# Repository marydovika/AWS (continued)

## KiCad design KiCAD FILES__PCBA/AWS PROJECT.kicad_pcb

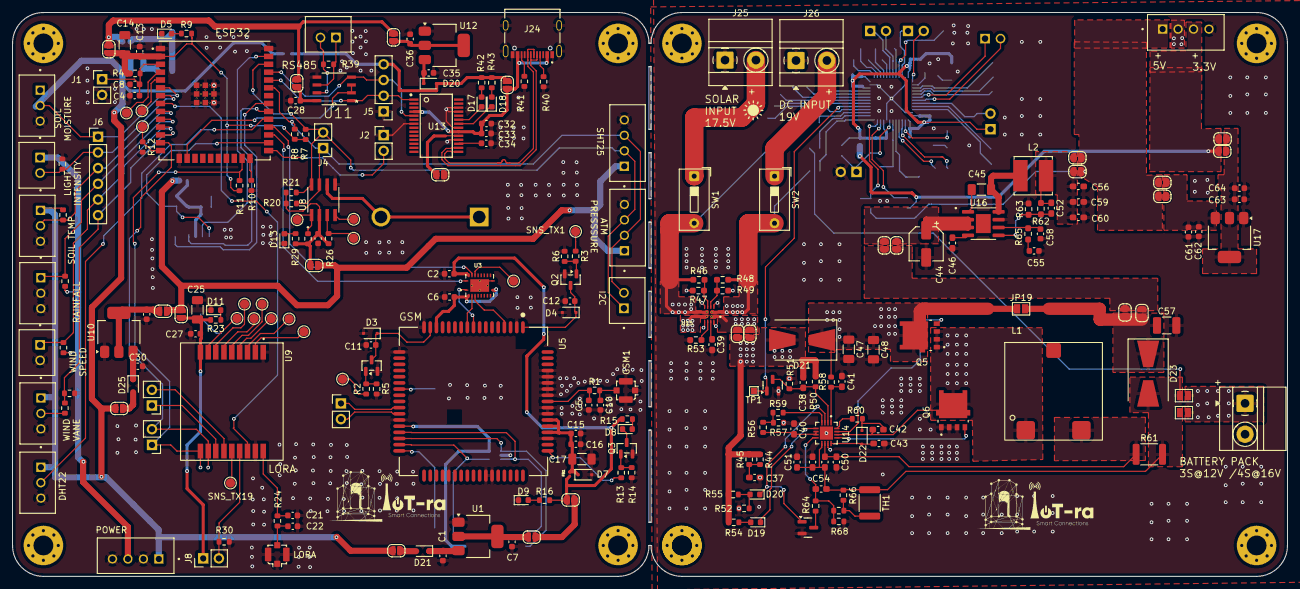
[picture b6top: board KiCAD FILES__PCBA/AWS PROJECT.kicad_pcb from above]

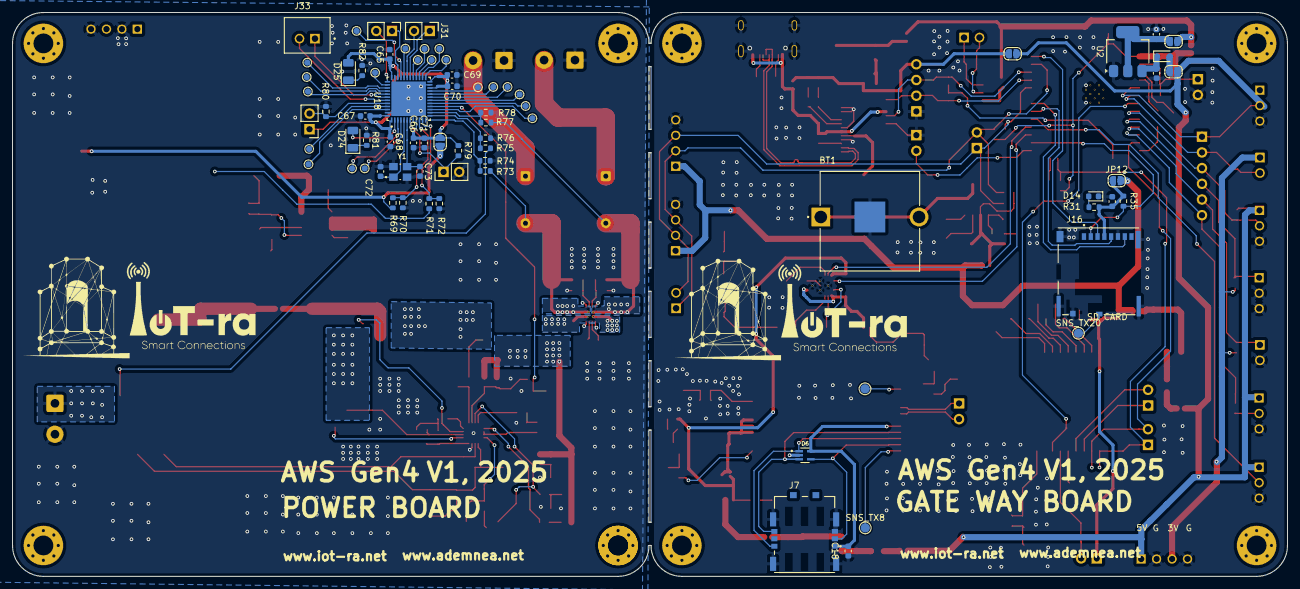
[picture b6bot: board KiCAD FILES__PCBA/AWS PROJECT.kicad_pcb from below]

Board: 2 copper layers, 206.3 x 91.2 mm, 308 parts (74 on the bottom side), 199 nets.

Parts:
BT1: BHX1-1225-PC; BAT_BHX1-1225-PC
C1, C3, C30, C35, C61, C62: 10uF; C_0603_1608Metric
C2, C4, C6, C11, C12, C13, C15, C18, C26, C27, C28, C33, C34, C65, C67, C69, C70: 0.1uF; C_0603_1608Metric
C5, C10, C21, C22: Cm; C_0603_1608Metric
C7, C8, C9, C16, C29, C31, C36, C63, C64: 1uF; C_0603_1608Metric
C14: 22uF; C_1206_3216Metric_Pad1.33x1.80mm_HandSolder
C17: 100uF; C_1206_3216Metric_Pad1.33x1.80mm_HandSolder
C25, C47, C48: 10uF; C_1206_3216Metric_Pad1.33x1.80mm_HandSolder
C32, C68, C71: 4.7uF; C_0603_1608Metric
C37, C49: 2.2uF; C_0603_1608Metric_Pad1.08x0.95mm_HandSolder
C38, C54: 22pF; C_0603_1608Metric_Pad1.08x0.95mm_HandSolder
C39: 0.01uF; C_0603_1608Metric_Pad1.08x0.95mm_HandSolder
C40, C41, C43, C53: 1uF; C_0603_1608Metric_Pad1.08x0.95mm_HandSolder
C42: 0.1uf; C_0603_1608Metric_Pad1.08x0.95mm_HandSolder
C44: 10uF; CP_Elec_5x5.8
C45: 100nF; C_1206_3216Metric_Pad1.33x1.80mm_HandSolder
C46: 10nF; C_0603_1608Metric_Pad1.08x0.95mm_HandSolder
C50: 0.1uF; C_0603_1608Metric_Pad1.08x0.95mm_HandSolder
C51: 10uF; C_0603_1608Metric_Pad1.08x0.95mm_HandSolder
C52: OPEN; C_0603_1608Metric_Pad1.08x0.95mm_HandSolder
C55: 2.7nF; C_0603_1608Metric
C56, C59, C60: 22uF; C_0603_1608Metric_Pad1.08x0.95mm_HandSolder
C57: 10uF; C_1210_3225Metric_Pad1.33x2.70mm_HandSolder
C58: 33pF; C_0603_1608Metric
C66: 10nF; C_0603_1608Metric
C72, C73: 22pF; C_0603_1608Metric
D3, D4, D7, D22: PESDHC3D3V3U; D_SOD-323F
D5, D8, D9, D11, D13, D14, D17, D18, D19, D20#2: NET_LED; D_0603_1608Metric
D6: ESDA6V1W5; SOT65P210X110-5N
D20, D21, D24, D25: 1N5819WS; D_SOD-323
D21#2, D23: B540C-13-F; D_SMB-SMC_Universal_Handsoldering
D24#2: green; LED_1206_3216Metric
D25#2: red; LED_1206_3216Metric
FB1: FerriteBead_Small; BEADC0603X33N
GSM1, GSM2: U.FL-R-SMT(10); U.FL_Molex_MCRF_73412-0110_Vertical
J1, J2, J3, J4, J8, J9, J10, J29, J30, J31, J32: Conn_01x02_Pin; PinHeader_1x02_P2.54mm_Vertical
J5: Conn_01x04_Pin; PinHeader_1x04_P2.54mm_Vertical
J6: Conn_01x06_Pin; PinHeader_1x06_P2.54mm_Vertical
J7: 104224-0820; MOLEX_104224-0820
J11, J15, J17, J28: B4B-XH-A_LF__SN_; JST_B4B-XH-A_LF__SN_
J12, J18, J19, J20, J22: B3B-XH-A_LF__SN_; JST_B3B-XH-A_LF__SN_
J13, J14, J21, J23, J33: B2B-XH-A_LF__SN_; JST_B2B-XH-A_LF__SN_
J16: 503398-1892; MOLEX_503398-1892
J24: TYPE-C-31-M-12; HRO_TYPE-C-31-M-12
J25, J26, J27: Screw_Terminal_01x02; TerminalBlock_MetzConnect_Type011_RT05502HBWC_1x02_P5.00mm_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
JP1, JP2, JP3, JP4, JP5, JP6, JP8, JP9, JP10, JP10#2, JP11, JP11#2, JP12, JP12#2, JP13, JP13#2, JP14, JP15, JP16, JP17, JP18, JP18#2, JP19#3, JP20, JP21, JP22, JP23, JP24, JP25: Jumper_2_Small_Open; SolderJumper-2_P1.3mm_Open_RoundedPad1.0x1.5mm
JP19, JP19#2, JP21#2: Jumper_2_Small_Open; SolderJumper-2_P1.3mm_Open_Pad1.0x1.5mm
L1: 6.1uH; CDEP147NP-6R1MC-95
L2: SRN6045TA-3R3Y; L_Bourns_SRN6045TA
PB1, PB2, PB3, PB4, PB5, PB6, PB7, PB8, PB9, PB10, PB11, PB12, PB13, PB14, PB15, PB16, PB17, PB18, PB19, PB20, PB21: TestPoint; TestPoint_Pad_D1.0mm
Q1, Q2, Q3: MMBT3904; SOT-23
Q4, Q7: 2N7002; Q_SOT-23
Q5, Q6: NMOS; TRANS_NVMFS5834NLWFT1G
R1, R24: 0R; R_0603_1608Metric
R2, R3, R5, R6, R7, R8, R13, R14, R20, R21, R25, R26, R32, R33, R38: 4.7k; R_0603_1608Metric
R4, R10, R11, R12, R30, R34: 10k; R_0603_1608Metric
R9, R15, R16, R23, R29, R31, R35: 1k; R_0603_1608Metric
R36: 20K; R_0603_1608Metric
R37, R54, R55, R69, R71, R73, R75, R77, R79, R80, R82: 10K; R_0603_1608Metric
R39: 120; R_0603_1608Metric
R40, R41: 5.1k; R_0603_1608Metric
R42, R43: 270R; R_0603_1608Metric
R44, R45: 3.9; R_0603_1608Metric
R46, R48: 23.7k; R_0603_1608Metric_Pad0.98x0.95mm_HandSolder
R47, R49: 5k; R_0603_1608Metric_Pad0.98x0.95mm_HandSolder
R50: 499K; R_0603_1608Metric
R51: 36K; R_0603_1608Metric
R52: 25k; R_0603_1608Metric
R53: 51.1K; R_0603_1608Metric_Pad0.98x0.95mm_HandSolder
R56: 5.23k; R_0603_1608Metric
R57: 7.5k; R_0603_1608Metric
R58: 10; R_0603_1608Metric
R59: 100; R_0603_1608Metric
R60: 2.2; R_0603_1608Metric
R61: 10; R_1812_4532Metric
R62, R63, R65: 5K1; R_0603_1608Metric_Pad0.98x0.95mm_HandSolder
R64: 4.22M; R_0603_1608Metric
R66: 154k; R_0603_1608Metric
R67: 887k; R_0603_1608Metric
R68: 162k; R_0603_1608Metric
R70: 20k; R_0603_1608Metric
R72: 13k; R_0603_1608Metric
R74: 1.5K; R_0603_1608Metric
R76: 2k; R_0603_1608Metric
R78: 1.2K; R_0603_1608Metric
R81: 330; R_0603_1608Metric
SNS_TX1, SNS_TX2, SNS_TX3, SNS_TX4, SNS_TX5, SNS_TX6, SNS_TX7, SNS_TX8, SNS_TX9, SNS_TX10, SNS_TX11, SNS_TX12, SNS_TX13, SNS_TX14, SNS_TX15, SNS_TX16, SNS_TX17, SNS_TX18, SNS_TX19, SNS_TX20: TestPoint; TestPoint_Pad_D1.5mm
SW1, SW2: SW_SPST; SW_DIP_SPSTx01_Slide_9.78x4.72mm_W7.62mm_P2.54mm
TH1: 100k; R_1812_4532Metric
TP1: TestPoint; TestPoint_Pad_1.0x1.0mm
U1, U2, U10, U12, U17: AMS1117-3.3; SOT-223-3_TabPin2
U3: TXB0108RGYR; IC_TXB0108RGYR
U4: ESP32-WROOM-32E__4MB_HIGH_TEMP_; MODULE_ESP32-WROOM-32UE_M113EH6400UH3Q0_
U5: SIM7000E; SIMCON_SIM7000E
U8: DS3231MZ_TRL; SOIC127P600X175-8N
U9: Ai-Thinker RA-08H; RA-08H
U11: ST3485EBDR; SOIC127P600X175-8N
U13: FT232RL-REEL; SOP65P780X200-28N
U14: BQ24650RVAR; QFN50P350X350X100-17N
U15: TPS2121RUXR; IC_TPS2121RUXR
U16: AP64501SP-13; SOIC127P600X170-9N
U18: STM32F401CCU6; QFN50P700X700X60-49N
Y1: C3E-25.000-12-3030-X-R; XTAL_C3E-25.000-12-3030-X-R

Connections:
3v3: J14.1, J15.3, R32.2, R33.2
5v: D20.2 (A), J5.4, J15.1, J18.1, J19.1, J20.1, J22.1, JP1.2 (B), JP2.2 (B), JP10#2.1 (A), JP10#2.2 (B), JP13.2 (B), JP15.2 (B), R38.2, R42.2, R43.2
+3.3V: J28.3, JP21.2 (B), JP24.2 (B), JP25.2 (B), R69.1
+3.3V_ESP: JP4.2 (B), JP5.2 (B), JP11#2.2 (B), JP16.2 (B)
+3.3V_GSM: JP3.2 (B), JP6.2 (B)
+3.3V_LORA: J11.1, J17.1, JP8.2 (B), JP10.2 (B), JP12#2.2 (B), JP14.2 (B)
+5V: J28.1, JP9.2 (B), JP12.2 (B), JP22.2 (B), JP23.2 (B), R71.1
/gate way/32khz: R25.1, SNS_TX11.1, U8.1 (32KHZ)
/gate way/-rs485 en: U4.16 (IO13), U11.2 (~RE), U11.3 (DE)
/gate way/D+: J3.1, U5.27 (USB_DP)
/gate way/D-: J3.2, U5.28 (USB_DM)
/gate way/DAVIS 7852: J6.4, J12.1, R32.1, U4.10 (IO25)
/gate way/DHT22: J22.2, U4.29 (IO5)
/gate way/DS18B20: J6.3, J20.2, R38.1, U4.9 (IO33)
/gate way/ESP32 power in: C13.1, C14.1, JP5.1 (A), R4.1, R7.2, R8.2, R9.2, R11.1, U4.2 (3V3)
/gate way/ESP_RX: U3.20 (B1), U4.27 (IO16)
/gate way/ESP_TX: U3.18 (B2), U4.28 (IO17)
/gate way/GSM_pw in: C2.1, FB1.2, JP6.1 (A), R15.2, R16.2, U3.19 (VCCB)
/gate way/I2C SCL: J4.2, J11.3, J17.2, J23.1, R7.1, R21.1, U4.36 (IO22), U8.8 (SCL)
/gate way/I2C SDA: J4.1, J11.2, J17.3, J23.2, R8.1, R20.1, U4.33 (IO21), U8.7 (SDA)
/gate way/INSPEED VORTEX: J6.5, J13.1, R33.1, U4.11 (IO26)
/gate way/INSPEEED VANE: J6.6, R36.2, R37.2, U4.12 (IO27)
/gate way/LORA ANT: C21.1, R24.1, U9.18 (ANT)
/gate way/LORA BOOT: J8.2, R30.2, U9.15 (IO2/BOOT)
/gate way/LORA RST: U4.8 (IO32), U9.16 (RST)
/gate way/LORA_RX: J10.2, U4.13 (IO14), U9.11 (TXD/IO17)
/gate way/LORA_TX: J10.1, R11.2, U4.23 (IO15), U9.10 (LPRXD/IO60)
/gate way/RI: SNS_TX5.1, U3.17 (B3)
/gate way/RS485 power in: C28.1, JP11#2.1 (A), U11.8 (VCC)
/gate way/RTC INT: R26.1, SNS_TX10.1, U8.3 (~INT/SQW)
/gate way/RTC RST: SNS_TX9.1, U8.4 (~RST)
/gate way/RTC power input: C26.1, JP10.1 (A), R20.2, R21.2, R25.2, R26.2, R29.2, U8.2 (VCC)
/gate way/S1223: J6.2, J14.2, R34.2, U4.7 (IO35)
/gate way/SD CS: J16.2 (CD/DAT3^2), R35.1, U4.26 (IO4)
/gate way/SD power in: C29.1, J16.4 (VDD), JP12#2.1 (A), R31.2, R35.2
/gate way/SIM CLK: D6.1, J7.S3 (CLK), U5.32 (SIM_CLK)
/gate way/SIM DATA: D6.3, J7.S6 (I/O), U5.31 (SIM_DATA)
/gate way/SIM DET: SNS_TX8.1, U5.34 (SIM_DET)
/gate way/SIM RST: D6.4, J7.S2 (RST), U5.33 (SIM_RST)
/gate way/SIM VDD: C18.1, D6.5, J7.S1 (VCC), U5.30 (SIM_VDD)
/gate way/USBD+: J24.A6 (DP1), J24.B6 (DP2), U13.15 (USBDP)
/gate way/USBD-: J24.A7 (DN1), J24.B7 (DN2), U13.16 (USBDM)
/gate way/VDD_EXT: C6.1, U3.2 (VCCA), U3.10 (OE), U5.15 (VDD_EXT)
/gate way/VH400: J6.1, J19.2, U4.6 (IO34)
/gate way/VSPI-CLK: J16.5 (CLK), U4.30 (IO18)
/gate way/VSPI-MISO: J16.7 (DAT0), U4.31 (IO19)
/gate way/VSPI-MOSI: J16.3 (CMD), U4.37 (IO23)
/gate way/gsm power key: R3.1, SNS_TX1.1
/gate way/gsm reset: R2.1, SNS_TX2.1
/gate way/gsm rx: U3.3 (A2), U5.10 (RXD)
/gate way/gsm tx: U3.1 (A1), U5.9 (TXD)
/gate way/lora power in: C25.1, C27.1, J8.1, JP8.1 (A), R23.2, U9.9 (VCC)
/gate way/main ant: C5.1, R1.1, U5.60 (RF_ANT)
/gate way/netlight: R13.1, U5.52 (NETLIGHT)
/gate way/nreset: C11.1, D3.1, Q1.3 (C), U5.16 (~NRESET)
/gate way/pwkey: C12.1, D4.1, Q2.3 (C), U5.1 (~PWRKEY)
/gate way/ri: U3.4 (A3), U5.4 (RI)
/gate way/rx: J5.2, U4.34 (RXD0), U11.1 (RO), U13.1 (TXD)
/gate way/strap2: R10.1, U4.24 (IO2)
/gate way/strap12: R12.1, SNS_TX7.1, U4.14 (IO12)
/gate way/tx: J5.3, U4.35 (TXD0), U11.4 (DI), U13.5 (RXD)
/power board/3V3_INPUT: R69.2, R70.1, U18.10 (PA0)
/power board/5V_INPUT: R71.2, R72.1, U18.11 (PA1)
/power board/BATTERY BMS: J27.1, JP19.2 (B), JP21#2.2 (B)
/power board/BATT_INPUT: R75.2, R76.1, U18.13 (PA3)
/power board/BATT_VAL: C49.2, C51.1, C53.1, C54.1, D23.2 (A), JP21#2.1 (A), R61.2, R66.2, R75.1, TH1.1, U14.9 (SRN)
/power board/BOOT0_MCU: J30.2, R80.2, U18.44 (BOOT0)
/power board/BOOT1_MCU: PB21.1, U18.20 (PB2)
/power board/CE: Q4.1 (G), TP1.1, U18.16 (PA6)
/power board/DC JACK INPUT: R48.1, R73.1, SW2.2 (B), U15.2 (IN2), U15.2_1 (IN2)
/power board/DC_INPUT: R73.2, R74.1, U18.12 (PA2)
/power board/FB: C52.2, R62.2, R63.1, U16.5 (FB)
/power board/MCU_SCL: J33.1, U18.42 (PB6)
/power board/MCU_SDA: J33.2, U18.43 (PB7)
/power board/MUXOUT: C38.1, D21#2.2 (A), JP13#2.2 (B), JP18.2 (B), R44.2, R45.2, R50.2, R54.2, R55.2
/power board/OV1: R46.2, R47.1, U15.5 (OV1)
/power board/OV2: R48.2, R49.1, U15.4 (OV2)
/power board/RST_MCU: J29.1, R79.1, U18.7 (~RST)
/power board/SOLAR INPUT: R46.1, R77.1, SW1.2 (B), U15.7 (IN1), U15.7_1 (IN1)
/power board/SOLAR_INPUT: R77.2, R78.1, U18.14 (PA4)
/power board/SW_AP: C45.1, L2.1, U16.8 (SW)
/power board/btst: R60.2, U14.16 (BTST)
/power board/cin: C72.2, U18.5 (PH0-OSC_IN), Y1.1
/power board/cout: C73.2, U18.6 (PH1-OSC_OUT), Y1.3
/power board/hidriv: Q5.4 (G), U14.15 (HIDRV)
/power board/lodriv: Q6.4 (G), U14.13 (LODRV)
/power board/mpptset: C38.2, Q4.3 (D), R50.1, R51.2, U14.2 (MPPSET)
/power board/ph: C42.2, L1.1, Q5.1 (S), Q5.2 (S), Q5.3 (S), Q6.5_6 (D), U14.14 (PH)
/power board/regn: C43.1, D22.2, U14.12 (REGN)
/power board/srp: C49.1, C50.1, L1.2, R61.1, U14.10 (SRP)
/power board/stat1: D19.1 (K), U14.5 (STAT2)
/power board/stat2: D20#2.1 (K), Q7.1 (G), U14.3 (STAT1)
/power board/ts: R59.2, U14.4 (TS)
/power board/vfb: C54.2, R64.2, R67.1, R68.2, U14.8 (VFB)
/power board/vref: C40.1, R56.2, U14.6 (VREF), U14.7 (TERM_EN)
GND: BT1.2, C1.2, C2.2, C3.2, C4.1, C5.2, C6.2, C7.2, C8.2, C9.2, C10.2, C11.2, C12.2, C13.2, C14.2, C15.2, C16.2, C17.2, C18.2, C21.2, C22.2, C25.2, C26.2, C27.2, C28.2, C29.2, C30.2, C31.2, C32.2, C33.2, C34.2, C35.2, C36.2, C37.2, C39.2, C40.2, C41.2, C43.2, C44.2, C46.2, C47.2, C48.2, C50.2, C51.2, C53.2, C55.2, C56.2, C57.2, C58.2, C59.2, C60.2, C61.2, C62.2, C63.2, C64.2, C65.2, C66.2, C67.2, C68.2, C69.2, C70.2, C71.2, C72.1, C73.1, D3.2, D4.2, D5.1 (K), D6.2, D7.2, D9.1 (K), D11.1 (K), D13.1 (K), D14.1 (K), GSM1.2, GSM2.2, J1.2, J2.1, J5.1, J7.G1 (GND), J7.G2 (GND), J7.G3 (GND), J7.G4 (GND), J7.S4 (GND), J11.4, J12.2, J12.3, J13.2, J15.2, J15.4, J16.6 (VSS), J16.9 (VSS), J16.P1 (SHIELD), J16.P2 (SHIELD), J16.P3 (SHIELD), J16.P4 (SHIELD), J17.4, J18.3, J19.3, J20.3, J22.3, J24.A1_B12 (GND), J24.B1_A12 (GND), J24.S1 (SHIELD), J24.S2 (SHIELD), J24.S3 (SHIELD), J24.S4 (SHIELD), J25.1, J26.1, J27.2, J28.2, J28.4, J29.2, JP17.2 (B), Q1.2 (E), Q2.2 (E), Q3.2 (E), Q4.2 (S), Q6.1 (S), Q6.2 (S), Q6.3 (S), Q7.2 (S), R5.1, R6.1, R10.2, R12.2, R14.1, R30.1, R34.1, R36.1, R40.1, R41.1, R47.2, R49.2, R51.1, R52.1, R53.2, R57.1, R63.2, R68.1, R70.2, R72.2, R74.2, R76.2, R78.2, R80.1, R81.1, R82.1, U1.1 (GND), U2.1 (GND), U3.11 (GND), U3.21 (EXP), U3.21_1 (EXP), U3.21_2 (EXP), U3.21_3 (EXP), U3.21_4 (EXP), U4.1 (GND), U4.15 (GND), U4.38 (GND), U4.39_1 (GND), U4.39_2 (GND), U4.39_3 (GND), U4.39_4 (GND), U4.39_5 (GND), U4.39_6 (GND), U4.39_7 (GND), U4.39_8 (GND), U4.39_9 (GND), U5.2 (GND), U5.17 (GND), U5.18 (GND), U5.29 (GND), U5.39 (GND), U5.45 (GND), U5.46 (GND), U5.54 (GND), U5.58 (GND), U5.59 (GND), U5.61 (GND), U5.62 (GND), U5.63 (GND), U5.64 (GND), U5.65 (GND), U8.5 (GND), U9.1 (GND), U9.17 (GND), U10.1 (GND), U11.5 (GND), U12.1 (GND), U13.7 (GND), U13.18 (GND), U13.21 (GND), U13.25 (AGND), U13.26 (TEST), U14.11 (GND), U14.17 (EP), U15.3 (CP2), U15.6 (PR1), U15.9 (ST), U15.12 (GND), U16.7 (GND), U17.1 (GND), U18.8 (VSSA/VREF-), U18.23 (VSS), U18.35 (VSS), U18.47 (VSS), U18.49 (EXP), Y1.2 (GND), Y1.4 (GND)
unnamed: C10.1, GSM1.1, R1.2
unnamed: C15.1, C16.1, C17.1, D7.1, FB1.1, U5.55 (VBAT), U5.56 (VBAT), U5.57 (VBAT)
unnamed: C22.1, GSM2.1, R24.2
unnamed: C37.1, R44.1, R45.1
unnamed: C42.1, D22.1, R60.1
unnamed: C55.1, R65.1
unnamed: D5.2 (A), R9.1
unnamed: D8.2 (A), R15.1
unnamed: D8.1 (K), Q3.3 (C)
unnamed: D9.2 (A), R16.1
unnamed: D11.2 (A), R23.1
unnamed: D13.2 (A), R29.1
unnamed: D14.2 (A), R31.1
unnamed: D17.2 (A), R42.1
unnamed: D17.1 (K), U13.23 (CBUS0)
unnamed: D18.2 (A), R43.1
unnamed: D18.1 (K), U13.22 (CBUS1)
unnamed: D19.2 (A), R54.1
unnamed: D20#2.2 (A), R52.2, R55.1
unnamed: C47.1, C48.1, C57.1, D21#2.1 (K), D23.1 (K), JP18#2.1 (A), JP19#2.1 (A), JP19#2.2 (B), JP20.1 (A), Q5.5_6 (D), R58.2
unnamed: D24#2.2 (A), U18.2 (PC13)
unnamed: D24#2.1 (K), R81.2
unnamed: D25.2 (A), JP13.1 (A)
unnamed: D25#2.1 (K), R82.2
unnamed: C4.2, C8.1, J1.1, R4.2, U4.3 (EN)
unnamed: J2.2, U4.25 (IO0)
unnamed: J9.1, U9.12 (RXD/IO16)
unnamed: J9.2, U9.13 (IO15)
unnamed: J16.10 (DETECT_SWITCH), SNS_TX20.1
unnamed: J18.2, R37.1
unnamed: J24.A5 (CC1), R40.2
unnamed: J24.B5 (CC2), R41.2
unnamed: J25.2, SW1.1 (A)
unnamed: J26.2, SW2.1 (A)
unnamed: J31.1, U18.30 (PA9)
unnamed: J31.2, U18.31 (PA10)
unnamed: J32.1, U18.34 (PA13/JTMS-SWDIO)
unnamed: J32.2, U18.37 (PA14/JTCK-SWCLK)
unnamed: D24.2 (A), JP2.1 (A)
unnamed: C7.1, JP3.1 (A), U1.2 (VO)
unnamed: C9.1, JP4.1 (A), U2.2 (VO)
unnamed: JP13#2.1 (A), JP18.1 (A), U15.1 (OUT), U15.1_1 (OUT), U15.8 (OUT), U15.8_1 (OUT)
unnamed: C31.1, JP14.1 (A), U10.2 (VO)
unnamed: C36.1, JP16.1 (A), U12.2 (VO)
unnamed: JP17.1 (A), U13.19 (~RESET)
unnamed: C44.1, JP19#3.1 (A), U16.2 (VIN), U16.3 (EN)
unnamed: C52.1, C56.1, C59.1, C60.1, JP22.1 (A), L2.2, R62.1
unnamed: C61.1, C62.1, JP23.1 (A), U17.3 (VI)
unnamed: C63.1, C64.1, JP24.1 (A), U17.2 (VO)
unnamed: Q1.1 (B), R2.2, R5.2
unnamed: Q2.1 (B), R3.2, R6.2
unnamed: Q3.1 (B), R13.2, R14.2
unnamed: Q7.3 (D), R64.1
unnamed: R56.1, R57.2, R59.1
unnamed: R66.1, R67.2, TH1.2
unnamed: C1.1, D21.1 (K), U1.3 (VI)
unnamed: C3.1, D24.1 (K), U2.3 (VI)
unnamed: SNS_TX4.1, U4.5 (SENSOR_VN)
unnamed: SNS_TX3.1, U4.4 (SENSOR_VP)
unnamed: SNS_TX6.1, U5.24 (USB_VBUS)
unnamed: BT1.1, BT1.1_1, U8.6 (VBAT)
unnamed: SNS_TX17.1, U9.5 (IO4)
unnamed: SNS_TX18.1, U9.6 (IO5)
unnamed: SNS_TX14.1, U9.2 (IO8)
unnamed: SNS_TX16.1, U9.4 (IO9)
unnamed: SNS_TX15.1, U9.3 (IO11)
unnamed: SNS_TX19.1, U9.14 (IO14)
unnamed: SNS_TX12.1, U9.7 (SWC/IO7)
unnamed: SNS_TX13.1, U9.8 (SWD/IO6)
unnamed: C30.1, D25.1 (K), U10.3 (VI)
unnamed: J21.1, R39.2, U11.6 (A)
unnamed: J21.2, R39.1, U11.7 (B)
unnamed: C35.1, U12.3 (VI)
unnamed: C34.1, U13.17 (3V3OUT)
unnamed: C41.1, R58.1, U14.1 (VCC)
unnamed: R53.1, U15.10 (ILIM)
unnamed: C39.1, U15.11 (SS)
unnamed: C45.2, U16.1 (BST)
unnamed: C58.1, R65.2, U16.6 (COMP)
unnamed: C46.1, U16.4 (SS)
unnamed: PB1.1, U18.15 (PA5)
unnamed: PB2.1, U18.17 (PA7)
unnamed: PB3.1, U18.29 (PA8)
unnamed: PB5.1, U18.32 (PA11)
unnamed: PB4.1, U18.33 (PA12)
unnamed: PB6.1, U18.38 (PA15/JTDI)
unnamed: PB7.1, U18.18 (PB0)
unnamed: PB8.1, U18.19 (PB1)
unnamed: PB9.1, U18.39 (PB3/JTDO-SWO)
unnamed: PB10.1, U18.40 (PB4/~JTRST)
unnamed: PB11.1, U18.41 (PB5)
unnamed: PB12.1, U18.45 (PB8)
unnamed: PB13.1, U18.46 (PB9)
unnamed: PB14.1, U18.21 (PB10)
unnamed: PB15.1, U18.25 (PB12)
unnamed: PB16.1, U18.26 (PB13)
unnamed: PB17.1, U18.27 (PB14)
unnamed: PB18.1, U18.28 (PB15)
unnamed: PB19.1, U18.3 (PC14-OSC32_IN)
unnamed: PB20.1, U18.4 (PC15-OSC32_OUT)
VBUS: C32.1, C33.1, J24.A4_B9 (VBUS), J24.B4_A9 (VBUS), JP15.1 (A), U13.4 (VCCIO), U13.20 (VCC)
VDD: C65.1, C66.1, C67.1, C68.1, C69.1, C70.1, C71.1, D25#2.2 (A), J30.1, JP25.1 (A), R79.2, U18.1 (VBAT), U18.9 (VDDA/VREF+), U18.22 (VCAP_1), U18.24 (VDD), U18.36 (VDD), U18.48 (VDD)
Vbuck: JP11.2 (B), JP18#2.2 (B), JP19#3.2 (B), JP20.2 (B)

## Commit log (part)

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2025-10-31 schematic version 1
2025-11-01 finalised schematic
2025-11-03 first pcb draft
2025-11-06 finalised power schematic
2025-11-14 commit 111
2025-12-19 algorirthim design start
2025-12-19 algorithim dev
2025-12-19 Add lock file for schematic with hostname and username information
2025-12-19 Refactor code structure for improved readability and maintainability
2025-12-20 updates to the code and hardware, testing complete
2025-12-21 updates to gateway board
2025-12-26 updates to the power board
2025-12-31 changes tp gateway bosrd
2025-12-31 updates to pcb color
2025-12-31 comment
2025-12-31 refactoring folder
2025-12-31 ccommit 1
2025-12-31 changes to schematic
2026-01-01 further changes
2026-01-01 All files
    Adding all files from local drive
2026-01-01 re-organizing files
    organizing folders for readability
2026-01-01 re-naming folders from local drive
2026-01-01 assigning 3D foot prints
2026-01-01 adding system images for current design and previous design
2026-01-01 updating 3D footprints on PCB
2026-01-02 BOM used for prototyping
2026-01-02 Added project reports
2026-01-03 Prototype Report
2026-01-03 Update AWS Prototyping Report document
    Revised the AWS_Prototyping_Report.docx file with new content or corrections.
2026-01-04 modified Prototyping report
2026-01-05 Add Davis rain gauge functionality and update main setup
2026-01-06 Implement wind speed and direction sensor classes; update DAVIS class for improved rain gauge functionality
2026-01-07 fixed i2c error on pcb, added power monitoring code, tested all i2c slaves
2026-01-07 updates to the gateway board
2026-01-07 cosmetic updates to pcb boards
2026-01-07 RESTRUCTURING FILES
2026-01-08 MODIFACTIONS TO CASE DESIGN
2026-01-08 adding vents to case
2026-01-12 updates to main
2026-01-19 footprints, text, logo alignment and report
2026-01-26 updates to gsm code, connected to things speak,
2026-01-26 reset active layer to default in project configuration
2026-01-28 changes to pcb and 3d mdel
2026-01-29 updates to board
2026-02-02 deleting documents from public
2026-02-04 resolving merge
2026-02-04 Add research overview for AWS power electronics
    Added a detailed overview of the research on modular and adaptive power electronics for Automatic Weather Stations (AWS).
2026-02-04 Refactor README for clarity and formatting
2026-02-04 Fix spelling error in README.md
    Corrected spelling of 'energy' in the README.
2026-02-04 Fix typo in README.md
    Corrected the spelling of 'tailered' to 'tailored' in the README.
2026-02-04 Revise README for clarity on modular power system
    Updated the description of the modular power electronics system to clarify energy source integration and control strategy.
2026-02-04 Update README with project funding and deployment details
    Added funding information and details about field deployment.
2026-02-16 edits to the boards, got lcsc part numbers for bom, swapped unavailable components, fixed net label confilcts
2026-02-16 further updates to board
2026-02-21 updates to pcb board and creation of BOM
2026-04-28 Revise README for clarity on project objectives
    Refined system description for the modular and adaptive power electronics architecture for AWS. Enhanced clarity and structure in outlining the project's goals, methodologies, and expected outcomes.
2026-06-16 ErrorLogger: add header guard, includes and log filename
2026-06-16 ErrorLogger: add component identifier defines
2026-06-16 ErrorLogger: add error type defines for RTC, BME280, DHT22, DS18B20, power monitor
2026-06-16 ErrorLogger: add error type defines for GSM, LoRa, SD, SIM, WiFi, sensors, main loop
2026-06-16 ErrorLogger: add class declaration - header file complete
2026-06-16 fix gsm error
2026-06-16 ErrorLogger: add static members and begin() function
2026-06-16 ErrorLogger: add log() function
2026-06-16 ErrorLogger: add errorCount() and printLast() functions
2026-06-16 ErrorLogger: add timestamp, SD write and serial write functions - implementation complete
2026-06-16 ErrorLogger: integrate into RTC.cpp - log not found, power loss, NTP sync fail
2026-06-16 Data estimation in gsm
2026-06-16 adding wifi broadcasting to configure sleep mode
2026-06-16 changed wifi-name
2026-06-17 ErrorLogger: integrate into AIR_PRESSURE.cpp - log sensor not found
2026-06-17 ErrorLogger: integrate into DHT22.cpp - log temp and humidity NaN failures
2026-06-17 ErrorLogger: integrate into SOILTEMP.cpp - log sensor disconnection
2026-06-17 ErrorLogger: integrate into POWER_MONITORING.cpp - log I2C read incomplete
2026-06-17 ErrorLogger: integrate into GSM.cpp - log handshake failure
2026-06-17 ErrorLogger: integrate into LORA.cpp - log serial init failure
2026-06-17 ErrorLogger: integrate into DataLogger.cpp - log mount, write, parse and no-data failures
2026-06-17 Matching time of GSM and RTC
2026-06-17 ErrorLogger: add FILE_NOT_FOUND error type, fix clearFile() to use correct error code
2026-06-17 ErrorLogger: integrate into SIM.cpp - log restart, network, GPRS, reconnect, HTTP failures
2026-06-17 ErrorLogger: integrate into WIFI_CONNECTION.cpp - log timeout once after 30s without flooding log
2026-06-17 ErrorLogger: integrate into DAVIS.cpp - log ISR-null safely outside interrupt context
2026-06-17 ErrorLogger: integrate into WINDSPEED.cpp - log ISR-null, timeout, divide-by-zero
2026-06-17 ErrorLogger: integrate into main.cpp - begin(), BME280 NaN, power read fail
2026-06-17 working on the project algorithm
2026-06-18 made wifi name and password longer
2026-06-18 getting_exactTime
2026-06-22 Remove accidental AWS submodule reference
2026-06-22 Enhance error logging in DataLogger, GSM, and RTC modules; add new error types and improve handling of GSM time synchronization
2026-06-22 new definitions
2026-06-22 main.cpp
2026-06-22 rtc fix
2026-06-22 value check
2026-06-22 Enhance error logging in various modules; add end session logging and improve error handling for BME280 and LORA components
2026-06-23 sending sensor data to a database
2026-06-23 error with rtc time stamp fix
2026-06-23 All previous PCBA edits
2026-06-23 clean up
2026-06-23 revised design
2026-06-24 USSD Alert
2026-06-25 Serial.begin(115200)
2026-06-25 Update README with project description and funding info
    Added a brief description of the project and its funding.
2026-06-27 [1st] Updated component placement on pcb design.
2026-06-27 renamed two folders
2026-06-29 [2nd] Updated Component placement on pcb design.
